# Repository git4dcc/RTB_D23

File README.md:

# RTB_D23

The D23 decoder is a double sided mobile decoder with 8-pol NEM 652 connector. The decoder is designed to integrate into the [RTB](https://rtb4dcc.de/concept/) digital control infrastructure.

<details>
<summary>See also</summary>

- [RTB_D12 - custom](/../../../../git4dcc/RTB_D12) (Fleischmann V100)
- [RTB_D13 - custom](/../../../../git4dcc/RTB_D13) (Minitrix coach)
- [RTB_D15 - custom](/../../../../git4dcc/RTB_D15) (Minitrix V160)
- [RTB_D16 - NEM651](/../../../../git4dcc/RTB_D16)
- [RTB_D20 - NEM651](/../../../../git4dcc/RTB_D20)
- [RTB_D21 - Next18](/../../../../git4dcc/RTB_D21)
- [RTB_D22 - Plux16](/../../../../git4dcc/RTB_D22)

</details>

<details>
<summary>User Guides</summary>

- User Guide - DE
- [User Guide - EN](https://rtb4dcc.de/rtb_decoder_reference_en/)

</details>

<br>

## Decoder features,
- **NEM 652** connector
- **DCC**
  - DCC-A automatic logon
  - DCC-R protocol extension
  - Service Mode Programming
- **Railcom**
  - Channel 1/2
  - POM, xPOM
  - DYN: Speed, QoS, Track-voltage, Motor-current, AUX-current, Temp, Distance travelled
- Double sided
- Dimension: 19 x 12 mm
- 7-28V track voltage
- heartbeat LED
- adjustable max motor current (default 500mA)
- adjustable max AUX current (default 500mA)
- over temp protection
- Function output: LF/LR (dimmable, 1.4kHz) open drain
- Function output: AUX1 (dimmable, 1.4kHz) open drain via NEM 652 connector
- Function output: AUX2/AUX3/AUX4 open drain via solder pads
- Function output: AUX5/AUX6 logic level (3.3V) or ZBCLK/ZBDAT (3.3V)
- onboard buffer capacitor (2x 100uF/35V)
- <10mA idle power consumption
- Firmware update over main tracks via DCC-R protocol

# Hardware
The current PCB layout uses SMD footprints with 0.5mm pitch and 0402 parts. Reflow soldering is mandatory whereas handsoldering near to impossible.

## PCB
- 6-layer PCB, FR4, 18 x 12 x 0.8mm (double sided)
- CPU: AVR64DD28
- Motor bridge: DRV8231

## Kicad
[Schematic](doc/D23_schematic.pdf) | [Layout](doc/D23_layout.pdf) | [Gerber](gerber)

<details>
<summary>Dependency</summary>
<br>

:yellow_circle: Requires my Kicad project library [RTB_SamacSys](/../../../../git4dcc/RTB_SamacSys) in the same directory tree.

</details>

## Firmware
Filename structure: { **pcb** }{ **code** }{ **version** }.hex

Example: **D23F0001**.hex

|   | Description |
| --- | --- |
| **pcb** | Name of matching hardware (**D23**) |
| **code** | Type of code contained (**R**=rom, **B**=bootloader, **F**=flash, **U**=bld update, **P**=UPDI factory code) |
| **version** | Release version (**####**) |

[Firmware files](firmware)

## UPDI
The fuse settings as well as the P-code (D23Pxxxx.hex) has to be installed by using UPDI.<br>
Connecting the decoder via its track pins to a 5V(DC) power supply will boot its CPU. This way, its easy to program the fuses and flash.

<details>
<summary>Details</summary>

| Fuse Setting | P-code Install |
| --- | --- |
|||

</details>

# Images
| top | bottom |
| --- | --- |
|  |  |

# YouTube
Some YouTubes to see the D23 decoder in action.<br><br>

This project is intended for hobby use only and is distributed in accordance with the Apache License 2.0 agreement.

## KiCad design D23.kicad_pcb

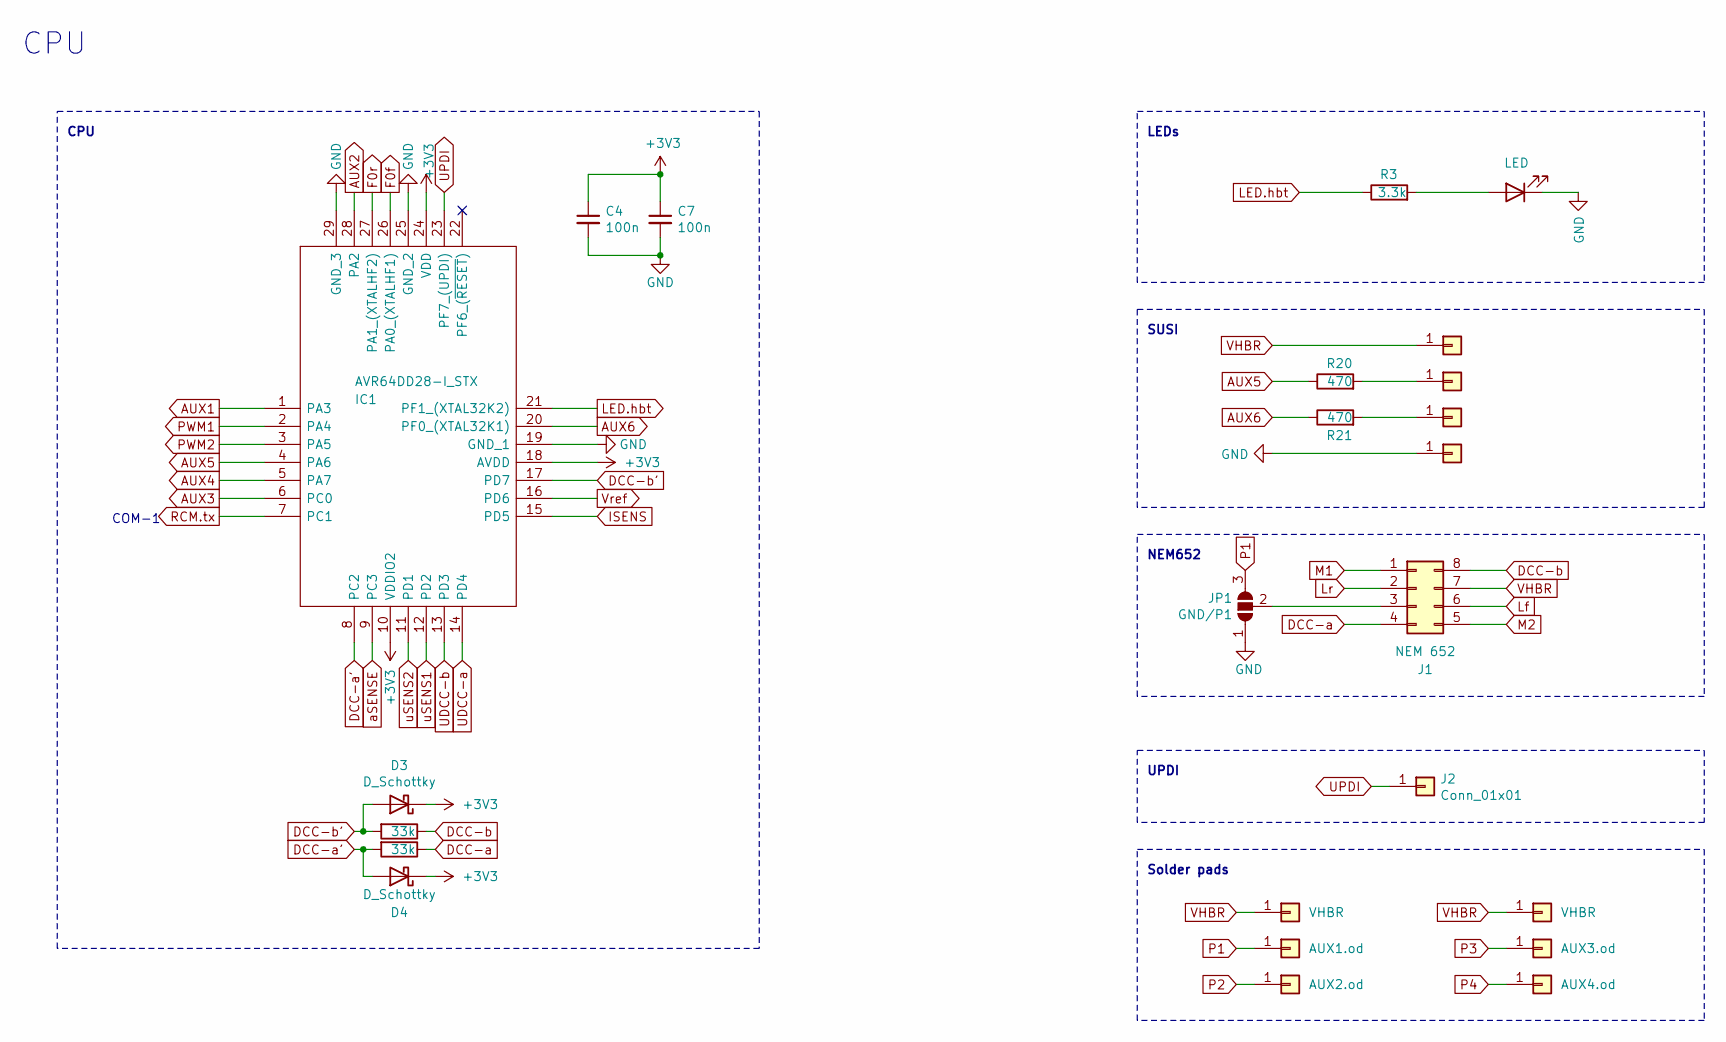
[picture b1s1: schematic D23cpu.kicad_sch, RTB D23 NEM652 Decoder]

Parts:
C4, C7: 100n; C_0402_1005Metric
D1: LED; LED_0402_1005Metric
D3, D4: D_Schottky; D_0201_0603Metric
IC1: AVR64DD28-I_STX; QFN-28-1EP_4x4mm_P0.4mm_EP2.3x2.3mm; Mouser Part Number 494-AVR64DD28-I/STX
J1: NEM 652; NEM-652
J2, J5, J6, J7, J11: Conn_01x01; DummyNet-Connector
J3: AUX1.od; DummyNet-Connector
J4: AUX2.od; DummyNet-Connector
J8, J12: VHBR; DummyNet-Connector
J9: AUX3.od; DummyNet-Connector
J10: AUX4.od; DummyNet-Connector
JP1: GND/P1; SolderJumper-3_P1.3mm_Open_Pad1.0x1.5mm
R1, R2: 33k; R_0402_1005Metric
R3: 3.3k; R_0402_1005Metric
R20, R21: 470; R_0402_1005Metric

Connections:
+3V3: C4.1, C7.1, D3.1 (K), D4.1 (K), IC1.10 (VDDIO2), IC1.18 (AVDD), IC1.24 (VDD); also elsewhere on the board
AUX1: IC1.1 (PA3); also elsewhere on the board
AUX2: IC1.28 (PA2); also elsewhere on the board
AUX3: IC1.6 (PC0); also elsewhere on the board
AUX4: IC1.5 (PA7); also elsewhere on the board
AUX5: IC1.4 (PA6), R20.1
AUX6: IC1.20 (PF0_(XTAL32K1)), R21.1
DCC-a: J1.4, R1.1; also elsewhere on the board
DCC-a': D4.2 (A), IC1.8 (PC2), R1.2
DCC-b: J1.8, R2.1; also elsewhere on the board
DCC-b': D3.2 (A), IC1.17 (PD7), R2.2
F0f: IC1.26 (PA0_(XTALHF1)); also elsewhere on the board
F0r: IC1.27 (PA1_(XTALHF2)); also elsewhere on the board
GND: C4.2, C7.2, D1.1 (K), IC1.19 (GND_1), IC1.25 (GND_2), IC1.29 (GND_3), J11.1, JP1.1 (A); also elsewhere on the board
ISENS: IC1.15 (PD5); also elsewhere on the board
LED.hbt: IC1.21 (PF1_(XTAL32K2)), R3.1
Lf: J1.6; also elsewhere on the board
Lr: J1.2; also elsewhere on the board
M1: J1.1; also elsewhere on the board
M2: J1.5; also elsewhere on the board
unnamed: D1.2 (A), R3.2
unnamed: J1.3, JP1.2 (C)
unnamed: J6.1, R20.2
unnamed: J7.1, R21.2
P1: J3.1, JP1.3 (B); also elsewhere on the board
P2: J4.1; also elsewhere on the board
P3: J9.1; also elsewhere on the board
P4: J10.1; also elsewhere on the board
PWM1: IC1.2 (PA4); also elsewhere on the board
PWM2: IC1.3 (PA5); also elsewhere on the board
RCM.tx: IC1.7 (PC1); also elsewhere on the board
UDCC-a: IC1.14 (PD4); also elsewhere on the board
UDCC-b: IC1.13 (PD3); also elsewhere on the board
UPDI: IC1.23 (PF7_(UPDI)), J2.1
VHBR: J1.7, J5.1, J8.1, J12.1; also elsewhere on the board
Vref: IC1.16 (PD6); also elsewhere on the board
aSENSE: IC1.9 (PC3); also elsewhere on the board
uSENS1: IC1.12 (PD2); also elsewhere on the board
uSENS2: IC1.11 (PD1); also elsewhere on the board

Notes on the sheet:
Solder pads
CPU
COM-1
LEDs
SUSI
NEM652
UPDI

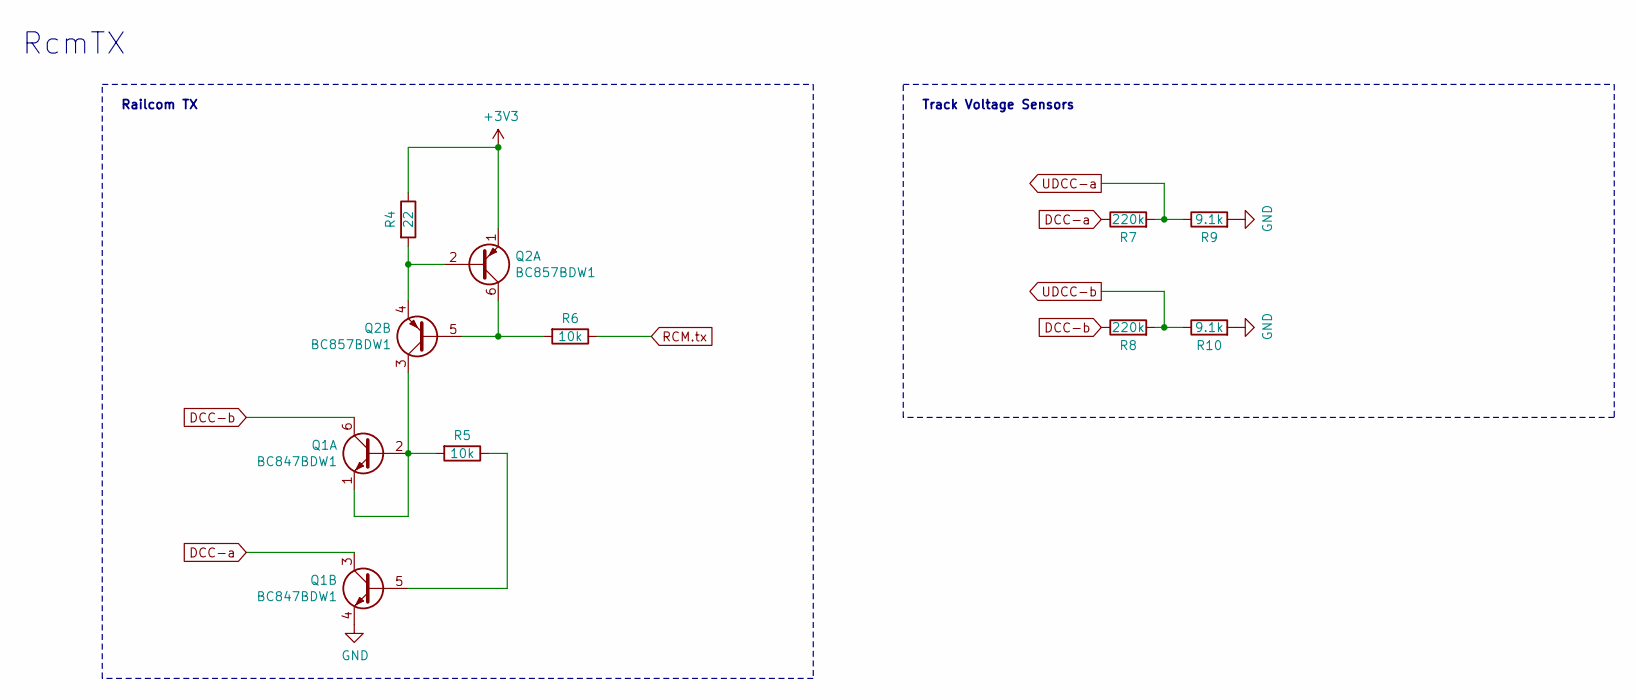
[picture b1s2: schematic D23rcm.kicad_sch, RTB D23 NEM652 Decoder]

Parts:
Q1: BC847BDW1; SOT-666
Q2: BC857BDW1; SOT-666
R4: 22; R_0402_1005Metric
R5, R6: 10k; R_0402_1005Metric
R7, R8: 220k; R_0402_1005Metric
R9, R10: 9.1k; R_0402_1005Metric

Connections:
+3V3: Q2.1 (E1), R4.1; also elsewhere on the board
DCC-a: Q1.3 (C2), R7.1; also elsewhere on the board
DCC-b: Q1.6 (C1), R8.1; also elsewhere on the board
GND: Q1.4 (E2), R9.2, R10.2; also elsewhere on the board
unnamed: Q1.1 (E1), Q1.2 (B1), Q2.3 (C2), R5.2
unnamed: Q1.5 (B2), R5.1
unnamed: Q2.2 (B1), Q2.4 (E2), R4.2
unnamed: Q2.5 (B2), Q2.6 (C1), R6.2
RCM.tx: R6.1; also elsewhere on the board
UDCC-a: R7.2, R9.1; also elsewhere on the board
UDCC-b: R8.2, R10.1; also elsewhere on the board

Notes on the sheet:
Track Voltage Sensors
Railcom TX
RcmTX

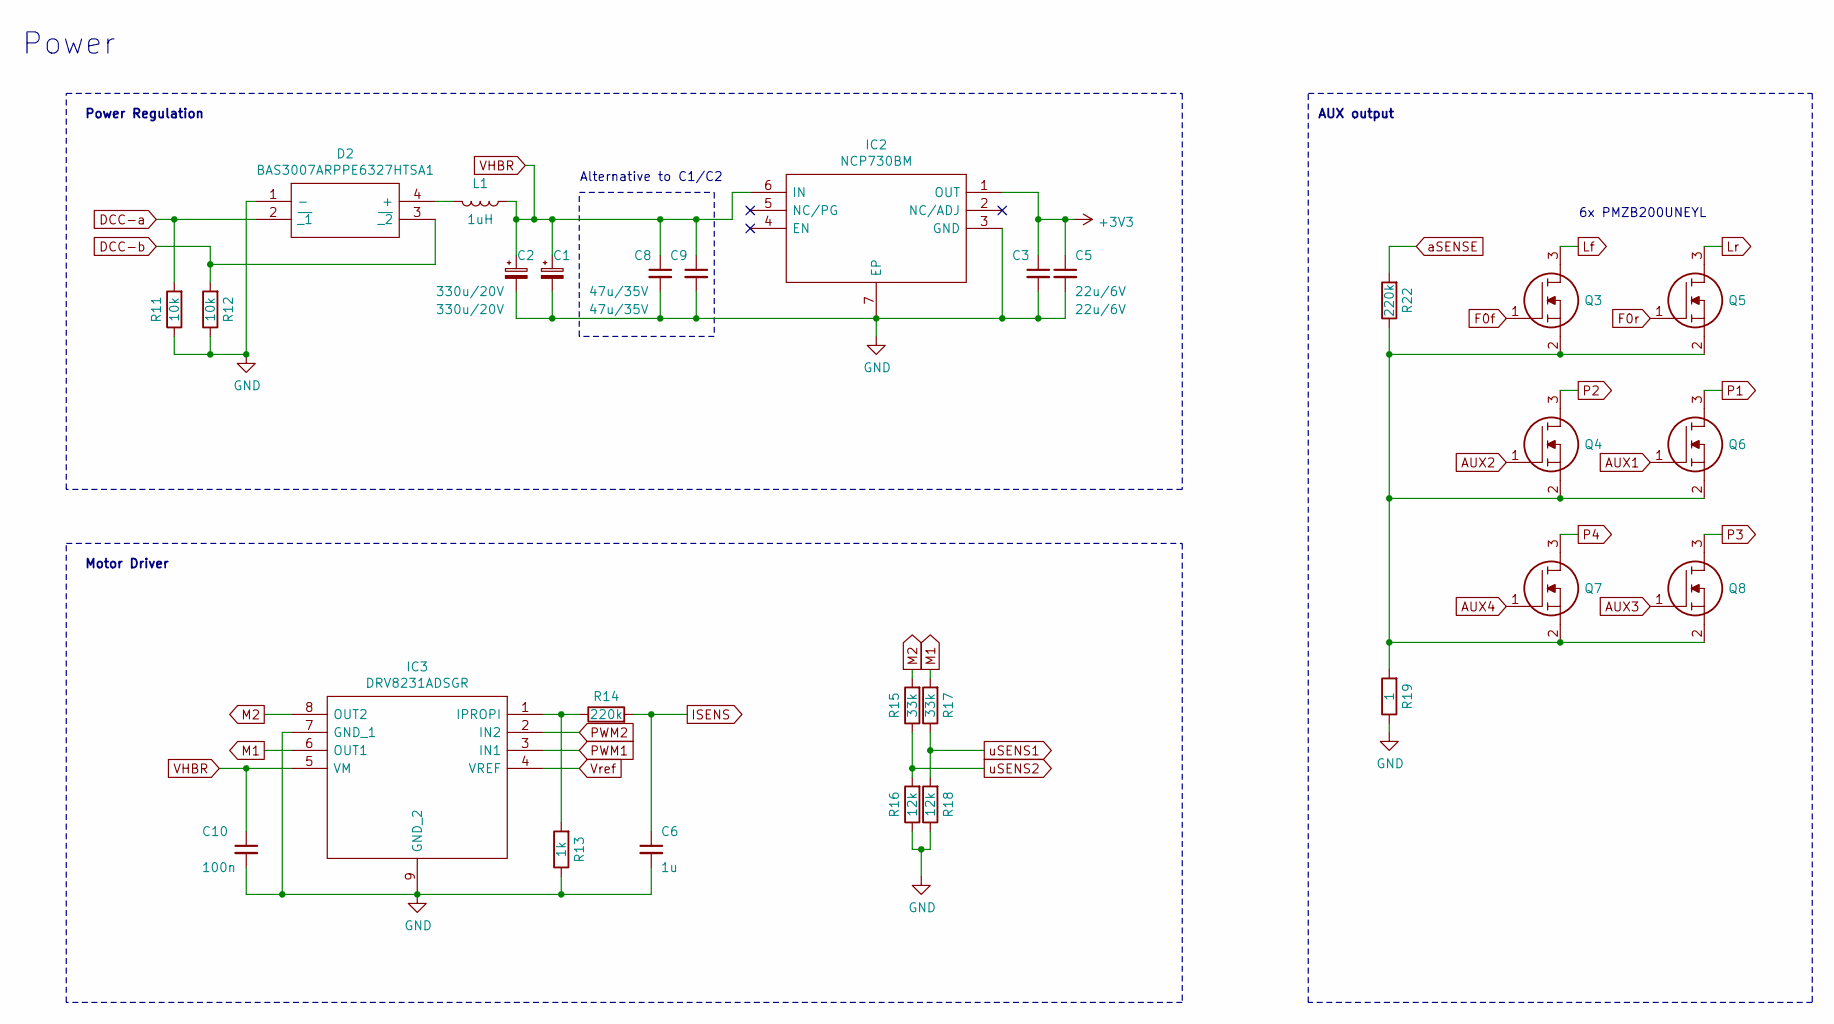
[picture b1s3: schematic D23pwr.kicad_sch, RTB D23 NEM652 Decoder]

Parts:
C1, C2: 330u/20V; CP_EIA-7361-438_AVX-U
C3, C5: 22u/6V; C_0402_1005Metric
C6: 1u; C_0402_1005Metric
C8, C9: 47u/35V; C_1206_3216Metric
C10: 100n; C_0603_1608Metric
D2: BAS3007ARPPE6327HTSA1; BF998215; Mouser Part Number 726-BAS3007A-RPPE6
IC2: NCP730BM; WSON-6-1EP_2x2mm_P0.65mm_EP1x1.6mm_ThermalVias; Mouser Part Number 863-NCP730BMT330TBG
IC3: DRV8231ADSGR; SON50P200X200X80-9N; Mouser Part Number 595-DRV8231ADSGR
L1: 1uH; L_0402_1005Metric
Q3, Q4, Q5, Q6, Q7, Q8: PMZB200UNEYL; Diodes_DFN1006-3; Mouser Part Number 771-PMZB200UNEYL
R11, R12: 10k; R_0402_1005Metric
R13: 1k; R_0402_1005Metric
R14, R22: 220k; R_0402_1005Metric
R15, R17: 33k; R_0402_1005Metric
R16, R18: 12k; R_0402_1005Metric
R19: 1; R_0603_1608Metric

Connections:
+3V3: C3.1, C5.1, IC2.1 (OUT); also elsewhere on the board
AUX1: Q6.1; also elsewhere on the board
AUX2: Q4.1; also elsewhere on the board
AUX3: Q8.1; also elsewhere on the board
AUX4: Q7.1; also elsewhere on the board
DCC-a: D2.2 (~_1), R11.2; also elsewhere on the board
DCC-b: D2.3 (~_2), R12.2; also elsewhere on the board
F0f: Q3.1; also elsewhere on the board
F0r: Q5.1; also elsewhere on the board
GND: C1.2, C2.2, C3.2, C5.2, C6.2, C8.2, C9.2, C10.2, D2.1 (-), IC2.3 (GND), IC2.7 (EP), IC3.7 (GND_1), IC3.9 (GND_2), R11.1, R12.1, R13.1, R16.1, R18.1, R19.1; also elsewhere on the board
ISENS: C6.1, R14.2; also elsewhere on the board
Lf: Q3.3; also elsewhere on the board
Lr: Q5.3; also elsewhere on the board
M1: IC3.6 (OUT1), R17.2; also elsewhere on the board
M2: IC3.8 (OUT2), R15.2; also elsewhere on the board
unnamed: D2.4 (+), L1.2
unnamed: IC3.1 (IPROPI), R13.2, R14.1
unnamed: Q3.2, Q4.2, Q5.2, Q6.2, Q7.2, Q8.2, R19.2, R22.1
P1: Q6.3; also elsewhere on the board
P2: Q4.3; also elsewhere on the board
P3: Q8.3; also elsewhere on the board
P4: Q7.3; also elsewhere on the board
PWM1: IC3.3 (IN1); also elsewhere on the board
PWM2: IC3.2 (IN2); also elsewhere on the board
VHBR: C1.1, C2.1, C8.1, C9.1, C10.1, IC2.6 (IN), IC3.5 (VM), L1.1; also elsewhere on the board
Vref: IC3.4 (VREF); also elsewhere on the board
aSENSE: R22.2; also elsewhere on the board
uSENS1: R17.1, R18.2; also elsewhere on the board
uSENS2: R15.1, R16.2; also elsewhere on the board

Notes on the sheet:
Motor Driver
Alternative to C1/C2
AUX output
Power Regulation
Power
6x PMZB200UNEYL

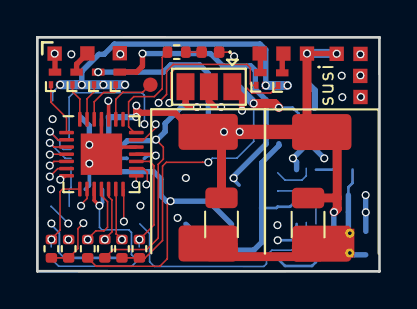
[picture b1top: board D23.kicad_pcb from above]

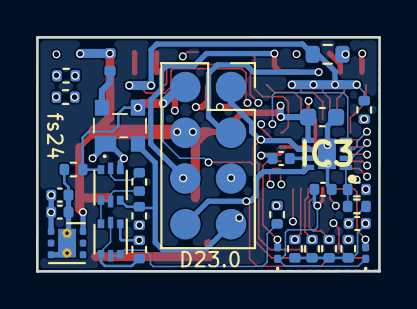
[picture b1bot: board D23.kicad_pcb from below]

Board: 6 copper layers, 19.0 x 13.0 mm, 61 parts (30 on the bottom side), 46 nets.

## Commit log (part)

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2025-03-17 initial
2025-03-22 add: decoder lock
2025-07-31 add: fuses
2025-07-31 add: updi description
2025-08-05 mod: led automation
2025-10-02 fix: SUSI/AUX
2026-02-20 git mirror test
2026-06-26 updated Kicad version
